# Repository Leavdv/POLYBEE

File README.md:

<h1> Connected Hive </h1>

<h2> Contributors </h2>

@LeaVdv, @Slyv06, @golddogh, @Nicolas-Charpentier, @Bees

<h2> Project description </h2>

The objective of this project is to provide remote monitoring of bee colonies (hives) in order to improve crop management. More precisely, our part deals with the development of a power supply board for internal modules with sensors. We must therefore be able to recharge LiFe batteries thanks to a photovoltaic panel in order to manage the autonomy of each hive as well as possible. We must also make a map for the link between the data received by each sensor in the apiary*. What we call the Gateway is the card that will send all values to a remotely searchable database.

*The grouping of hives is called an apiary.

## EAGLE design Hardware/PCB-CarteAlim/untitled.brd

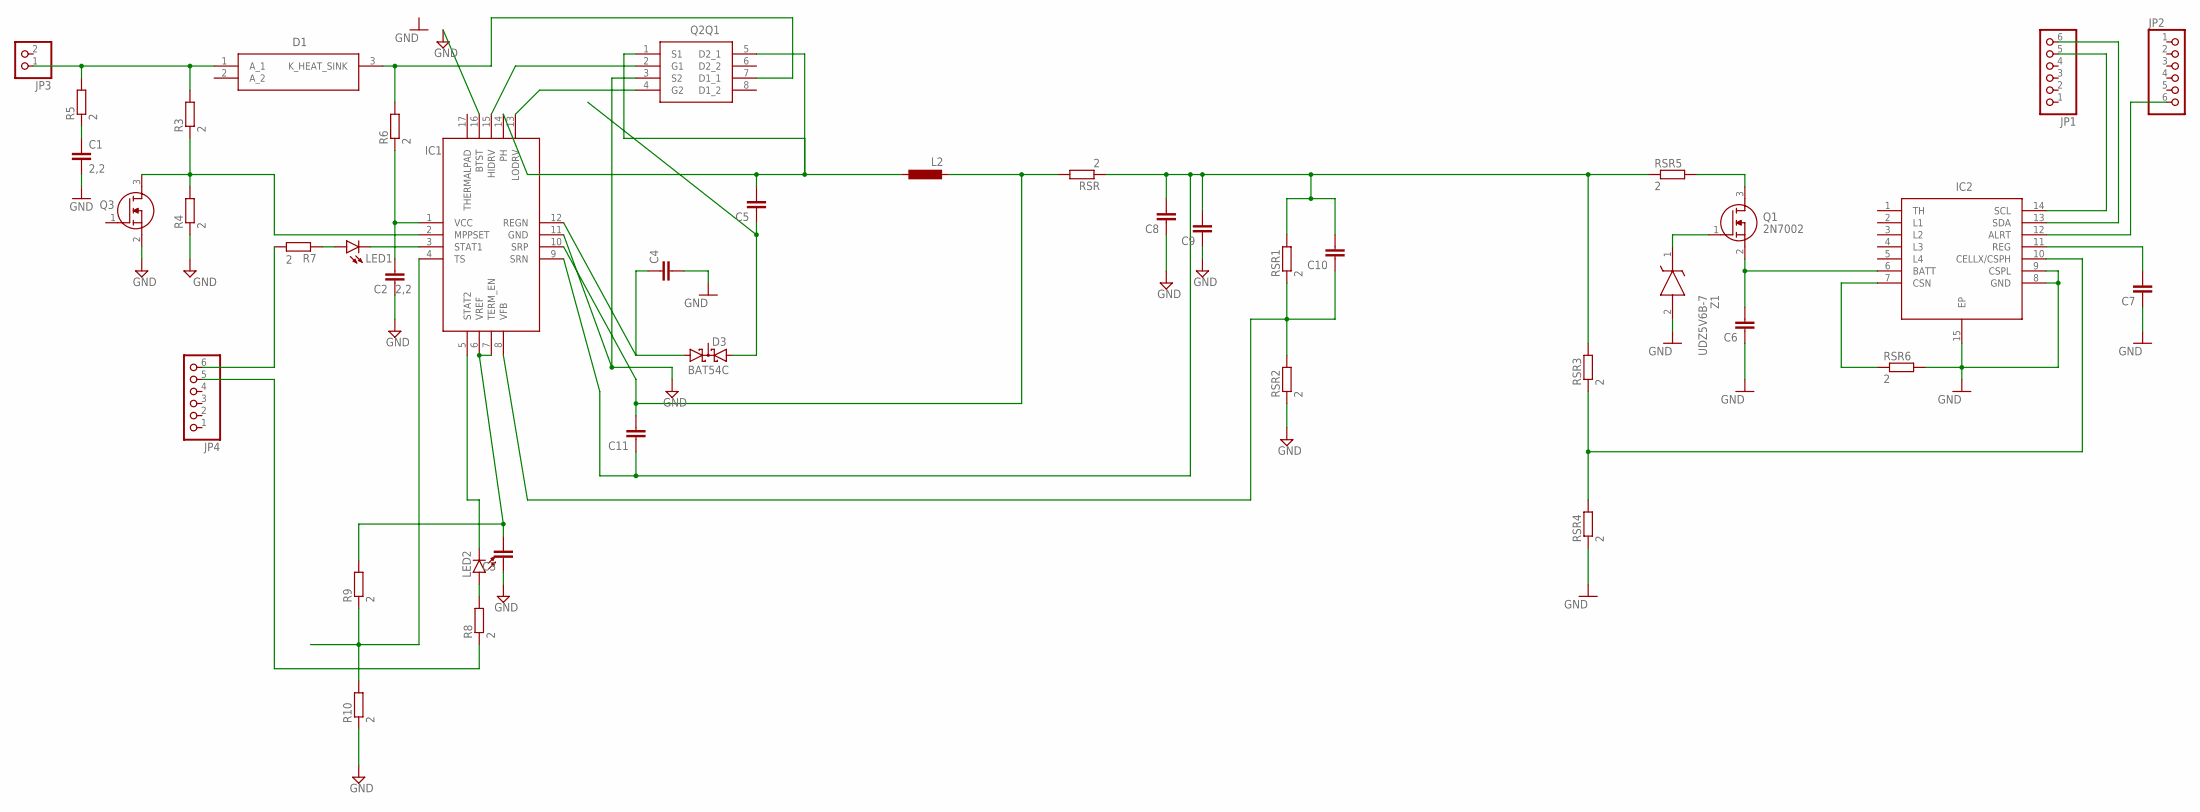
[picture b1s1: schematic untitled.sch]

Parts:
C1, C2, C3, C4, C5, C6, C7, C8, C9, C10, C11: 2,2; C0805K
D1: PDS1040Q-13; PDS104013
D3: BAT54C; SOT23
IC1: BQ24650RVAT; QFN50P350X350X100-17N
IC2: MAX17263LETD+; SON40P300X300X80-15N
JP1, JP2, JP4: PINHD-1X6; 1X06
JP3: PINHD-1X2; 1X02
L2: L-EUL2825P; L2825P
LED1, LED2: LAP4-BOTTOM; P47F-BOTTOM
Q1, Q3: 2N7002; SOT96P240X120-3N
Q2Q1: SI7288DP-T1-GE3; POWERPAK-SO8_1
R3, R4, R5, R6, R7, R8, R9, R10: 2; M1206
RSR, RSR1, RSR2, RSR3, RSR4, RSR5, RSR6: 2; M1206
Z1: UDZ5V6B-7; SOD2513X120N

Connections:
GND: C1.2, C2.1, C3.1, C4.2, C6.1, C7.1, C8.1, C9.1, IC1.11 (GND), IC1.16 (BTST), IC2.8 (GND), IC2.9 (CSPL), IC2.15 (EP), Q2Q1.3 (S2), Q3.2 (S), R4.1, R10.1, RSR2.1, RSR4.1, RSR6.2, Z1.2 (A)
unnamed: C4.1, D3.1 (A1), IC1.12 (REGN)
unnamed: C11.2, IC1.10 (SRP), L2.2, RSR.2
unnamed: IC2.14 (SCL), JP1.5
unnamed: C2.2, IC1.1 (VCC), R6.1
unnamed: C5.1, D3.2 (A2)
unnamed: IC1.2 (MPPSET), Q3.3 (D), R3.1, R4.2
unnamed: C1.1, R5.1
unnamed: LED1.A, R7.1
unnamed: C3.2, IC1.6 (VREF), IC1.7 (TERM_EN), R9.2
unnamed: C6.2, IC2.6 (BATT), Q1.2 (S)
unnamed: IC1.3 (STAT1), LED1.C
unnamed: C5.2, IC1.14 (PH), L2.1, Q2Q1.1 (S1), Q2Q1.5 (D2_1)
unnamed: IC1.5 (STAT2), LED2.C
unnamed: LED2.A, R8.2
unnamed: IC1.15 (HIDRV), Q2Q1.2 (G1)
unnamed: IC1.13 (LODRV), Q2Q1.4 (G2)
unnamed: Q1.1 (G), Z1.1 (K)
unnamed: D1.3 (K_HEAT_SINK), Q2Q1.7 (D1_1), R6.2
unnamed: Q1.3 (D), RSR5.2
unnamed: C7.2, IC2.11 (REG)
unnamed: C8.2, C9.2, C10.2, C11.1, IC1.9 (SRN), RSR.1, RSR1.2, RSR3.2, RSR5.1
unnamed: IC2.10 (CELLX/CSPH), RSR3.1, RSR4.2
unnamed: IC2.13 (SDA), JP1.6
unnamed: IC2.12 (ALRT), JP2.6
unnamed: C10.1, IC1.8 (VFB), RSR1.1, RSR2.2
unnamed: IC2.7 (CSN), RSR6.1
unnamed: D1.1 (A_1), JP3.1, R3.2, R5.2
unnamed: JP4.6, R7.2
unnamed: JP4.5, R8.1
R3: IC1.4 (TS), R9.1, R10.2

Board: 2 copper layers, 41 parts (0 on the bottom side), 31 nets, no tracks yet.

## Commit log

2019-11-08 Rename Readme.md to README.md
2019-11-13 Create Wifi
2019-12-13 Create Lien tuto ESP32 lora
2019-12-13 Rename Recherche Damien/Lien tuto ESP32 lora to Recherches Damien/Lien tuto ESP32 lora
2019-12-13 Update Lien tuto ESP32 lora
2019-12-13 Rename Lien tuto ESP32 lora to Librairies arduino
2019-12-13 Create Choix des librairies
2019-12-13 Update Librairies arduino
2019-12-13 Update Choix des librairies
2020-01-10 Create Utilisation de la librairie Lora
2020-01-17 Update Utilisation de la librairie Lora
